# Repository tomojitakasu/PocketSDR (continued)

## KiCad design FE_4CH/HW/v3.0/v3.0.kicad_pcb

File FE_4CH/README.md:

# **Pocket SDR FE 4CH - An Open-Source GNSS SDR RF Frontend**

## **Overview**

Pocket SDR FE 4CH is an open-source GNSS SDR RF frontend device for Pocket SDR.
The device consists of 4 CH Maxim MAX2771 ([1]) GNSS RF front-end ICs (LNA, mixer,
filter, ADC, frequency synthesizer) and a Cypress EZ-USB FX3 USB 3.0 controller
([2], [3], [4]) to connect to host PCs. All the RF CHs are able to be configured for
GNSS L1 band (1525 - 1610 MHz), or GNSS L2/L5/L6 band (1160 - 1290 MHz).
The frequency of the reference oscillator (TCXO) is 24.000 MHz, and the ADC
sampling rate can be configured up to 48 Msps.

--------------------------------------------------------------------------------

## **Specifications**

* **Number of RF Inputs**: 1 CH
* **Number of RF Channels**: 4 CH
* **LO (PLL) Frequency**: 1525 ~ 1610 MHz (GNSS L1 band) or
                      1160 ~ 1290 MHz (GNSS L2/L5/L6 band)
* **IF Bandwidth**: 2.5 ~ 36 MHz
* **Sampling Rate**: 4, 6, 8, 10, 12, 16, 20, 24, 32, 40 or 48 Msps
* **Sampling Type**: I-sampling 2 or 3 bits, I/Q-sampling 2 bits
* **Host I/F**: USB 3.0 (USB 3.2 Gen1, super-speed 5Gbps), type-C
* **Power Supply**: 5V 240 mA, USB bus power

--------------------------------------------------------------------------------

## **Directory Structure and Contents**
```
FE_4CH --+-- FW     Pocket SDR FE 4CH F/W and build environment
         |   |
         |   +-- Packages
         |   +-- v3.0
         |       +-- .metadata
         |       +-- .project
         |       +-- pocket_fw_v3    ver.3.0
         |           +-- pocket_fw_v3.c  Source program of the F/W
         |           +-- gpif_conf.cyfx  GPIF II Designer file for the F/W
         |           +-- gpif_conf.h     header file generated by GPIF II Designer
         |           +-- pocket_usb_dscr.c USB device descriptors for the F/W
         |           +-- cyfx*.*         Cypress FX3 F/W framework
         |           +-- ...              
         |           +-- Release
         |               +-- pocket_fw_v3.img  Binary image of the F/W
         |               +-- ...
         |
         +-- HW     Pocket SDR FE 4CH hardware design data
             |
             +-- v3.0     ver.3.0 (PCB 4-layer, USB type-C)
                 +-- v3.0.kicad.*     KiCAD PCB and circuit design data
                 +-- v3.0.pretty      KiCAD module data
                 +-- v3.0_parts.xlsx  BOM (parts list) Excel data
                 +-- pocket_sdr_v3.0_sch.pdf circuit schematic PDF
                 +-- pocket_sdr_*.f3d Case panel Fusion 360 3D-CAD data
                 +-- pocket_sdr_v2.3-eagle-import.kicad_sym  KiCAD symbol data
                 +-- ...
```
--------------------------------------------------------------------------------

## **Rebuild F/W and Write F/W Image to Pocket SDR FE 4CH**

* Install Cypress EZ-USB FX3 Development Kit (ref [5]) to a Windows PC. As default,
it is installed to C:\Program Files (x86)\Cypress\EZ-USB FX3 SDK.
* Execute EZ USB Suite (EZ-USB FX3 SDK\1.3\Eclipse\ezUsbSuite.exe).
* Execute Menu File - Switch Workspace - Others, select <install_dir>\PocketSDR\FE_4CH\FW\v3.0
and open the workspace.
* Select pocket_fw_v3 in Project Explorer and execute Menu Project - Build All and
you can get a F/W image <install_dir>\PocketSDR\FE_4CH\FW/v3.0\pocket_fw_v3\Release\pocket_fw_v3.img.
* Disable EEPROM by connecting the J2 jumper pins on the Pocket SDR FE 4CH PCB and
attach the Pocket SDR FE 4CH via USB cable to the PC.
* Execute USB Control Center (EZ-USB FX3 SDK\1.3\bin\CyControl.exe).
* You can see "Cypress FX3 USB BootLoader Device".
* Re-enable EEPROM by disconnecting the J2 jumper pins on the Pocket SDR FE 4CH PCB.
* In USB Control Center, select "Cypress FX3 USB Bootloader Device", execute menu
Program - FX3 - I2C EEPROM, select the F/W image <install_dir>\PocketSDR\FE_4CH\FW\v3.0\pocket_fw_v3\Release\pocket_fw_v3.img
and open it.
* If you see "Programming succeeded." in status bar, the F/W is properly written
to the PocketSDR FE 4CH.

--------------------------------------------------------------------------------

## **References**

[1] Maxim integrated, MAX2771 Multiband Universal GNSS Receiver, July 2018

[2] Infineon, CYUSB301X, CYUSB201X, EZ-USB FX3 SuperSpeed USB Controller Datasheet,
Rev. Z, September 29, 2022

[3] Cypress Semiconductor, EZ-USB FX3 Technical Reference Manual, Rev.F, May 9, 2019

[4] Cypress Semiconductor, FX3 Programmers Manual, Rev.K

[5] Infineon, EZ-USB FX3 Software Development Kit
    (https://www.infineon.com/cms/jp/design-support/tools/sdk/usb-controllers-sdk/ez-usb-fx3-software-development-kit/)

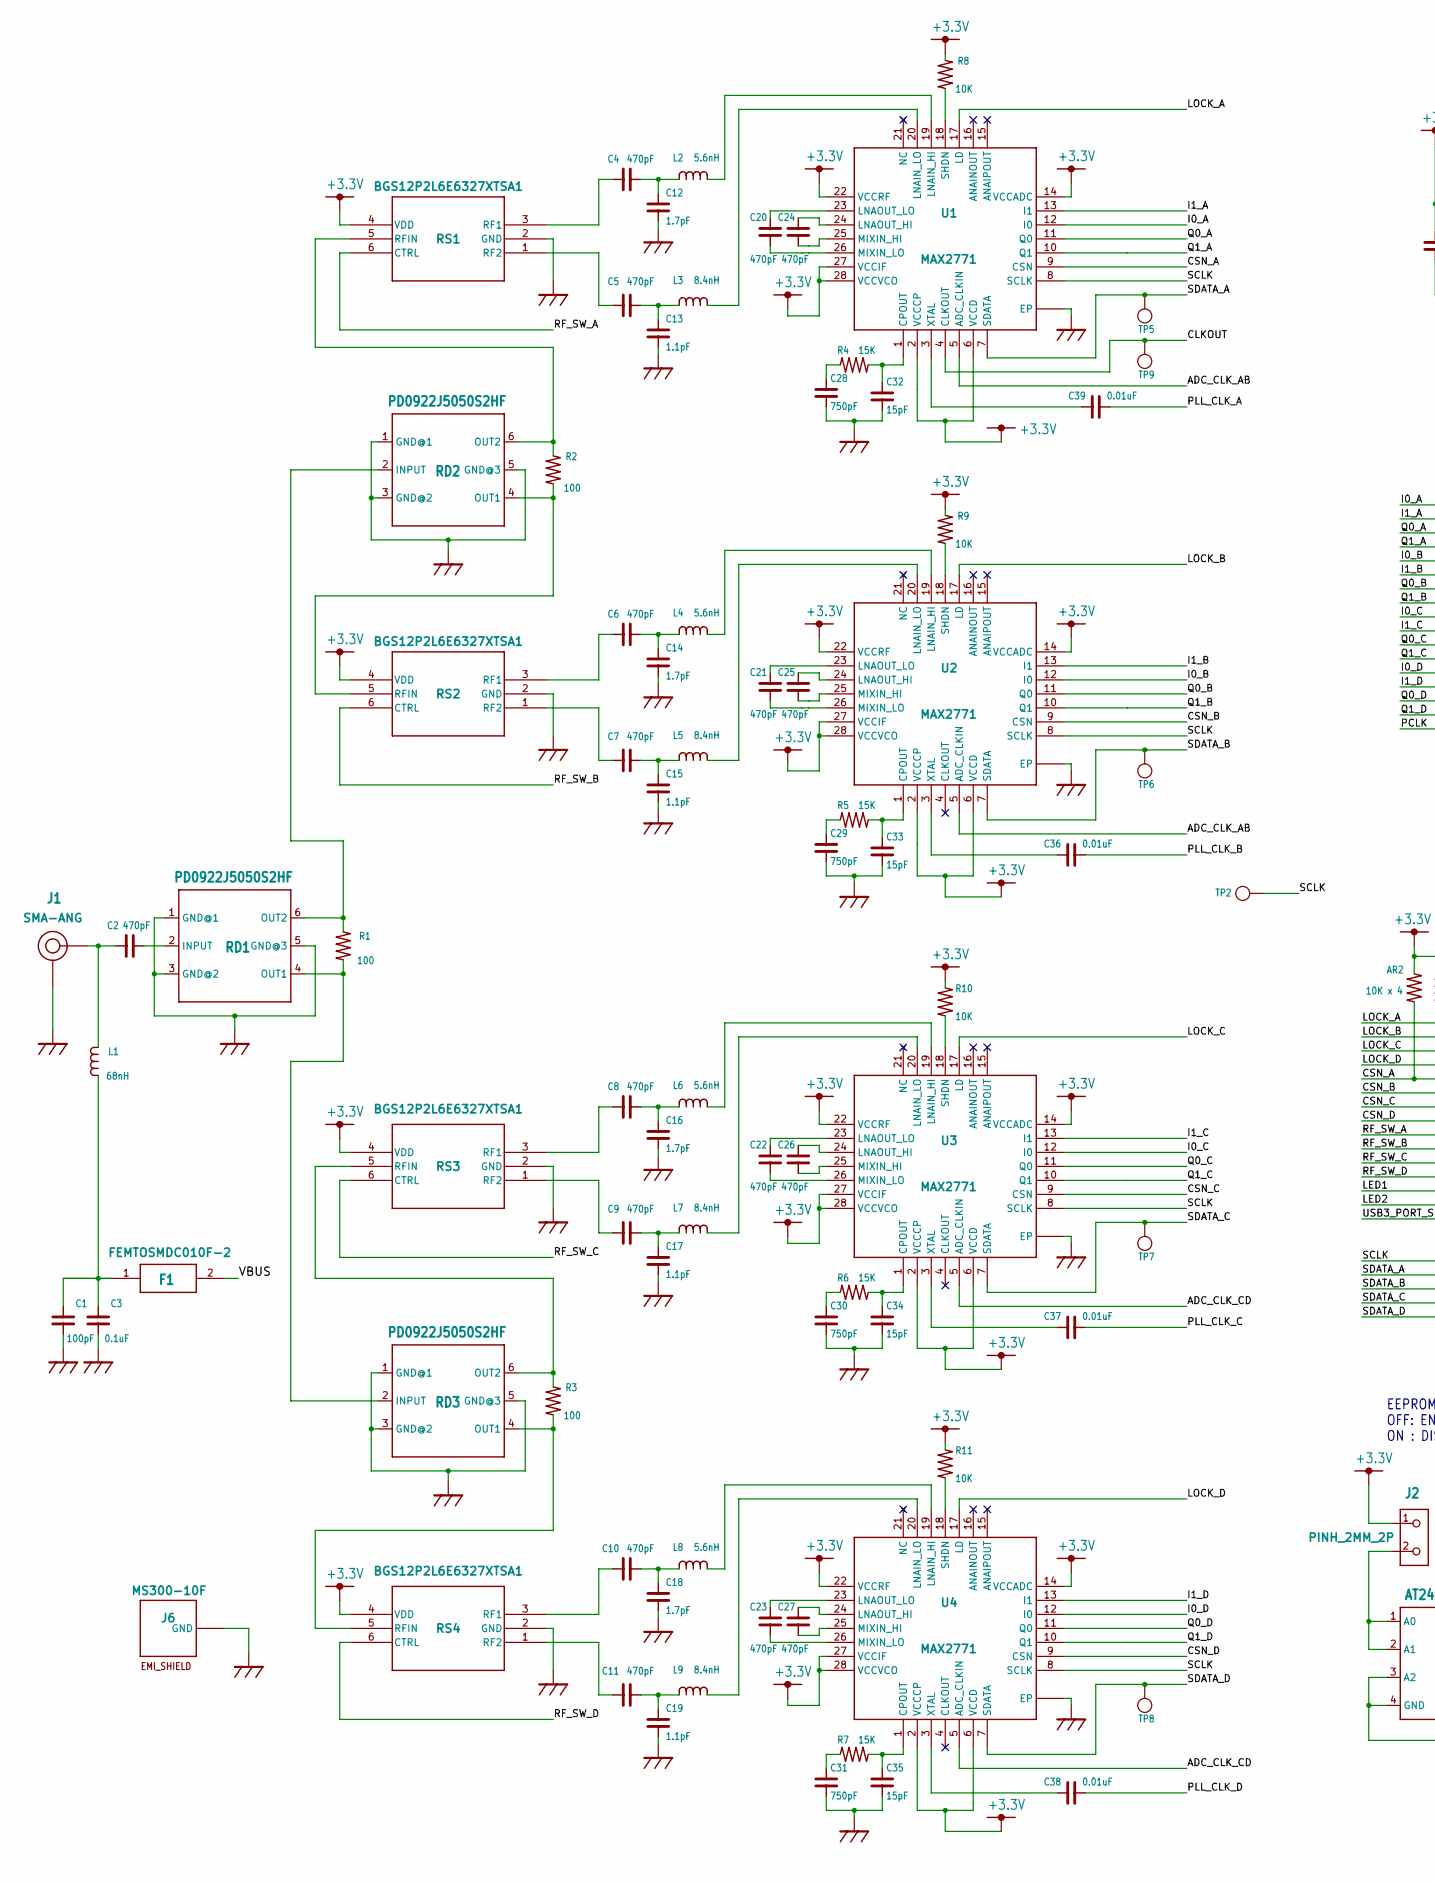
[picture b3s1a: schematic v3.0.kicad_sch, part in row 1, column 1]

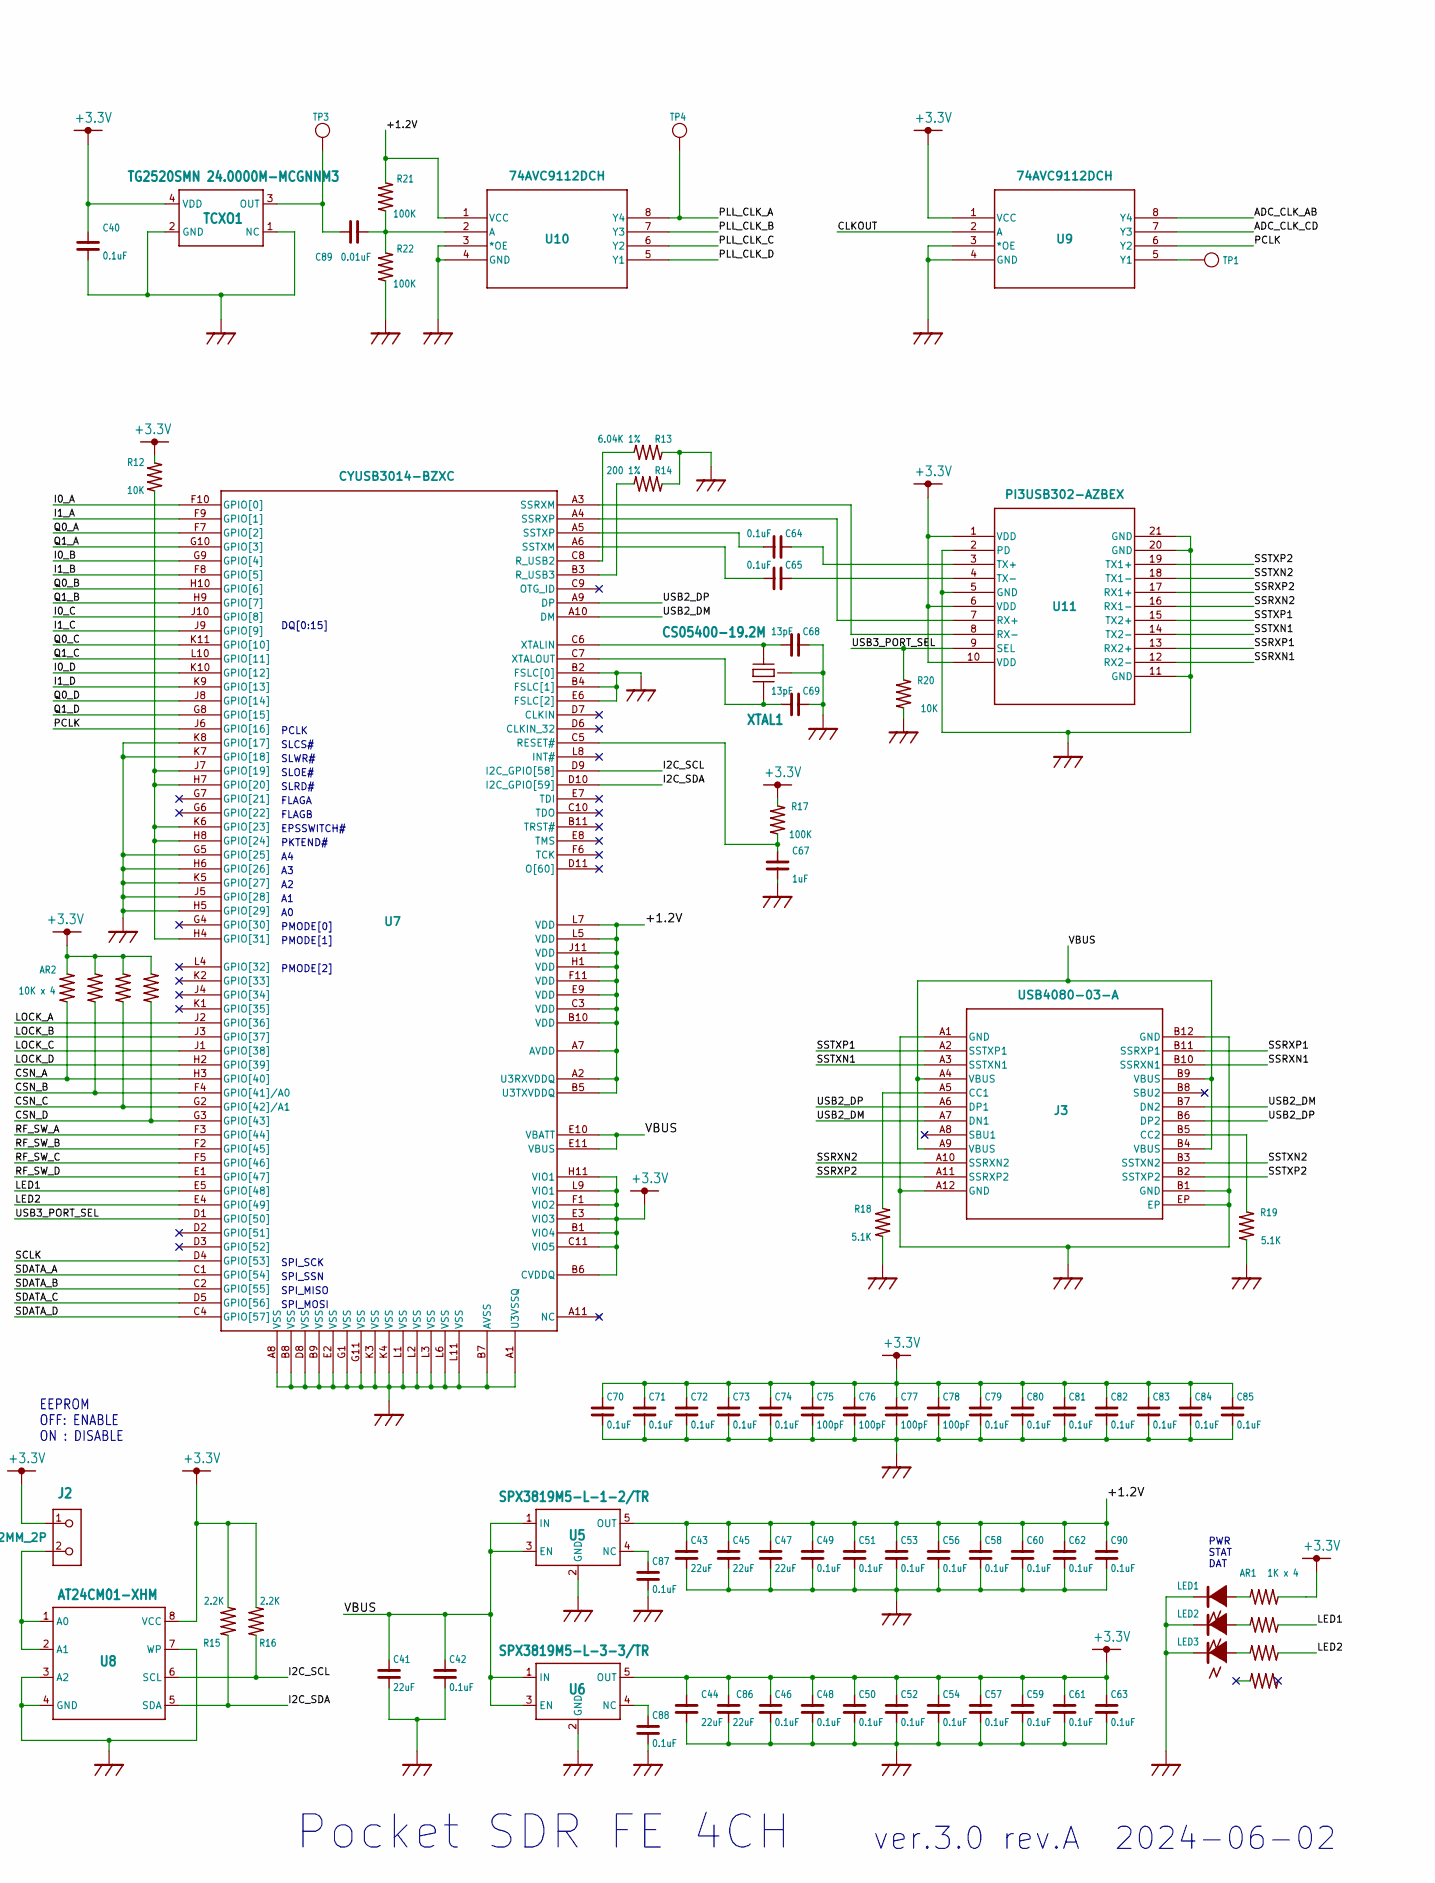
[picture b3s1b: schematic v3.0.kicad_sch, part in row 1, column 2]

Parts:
AR1: 1K x 4; EXB28V
AR2: 10K x 4; EXB28V
C1, C75, C76, C77, C78: 100pF; C1005
C2, C4, C5, C6, C7, C8, C9, C10, C11, C20, C21, C22, C23, C24, C25, C26, C27: 470pF; C1005
C3, C40, C42, C46, C48, C49, C50, C51, C52, C53, C54, C56, C57, C58, C59, C60, C61, C62, C63, C64, C65, C70, C71, C72, C73, C74, C79, C80, C81, C82, C83, C84, C85, C87, C88, C90: 0.1uF; C1005
C12, C14, C16, C18: 1.7pF; C1005
C13, C15, C17, C19: 1.1pF; C1005
C28, C29, C30, C31: 750pF; C1005
C32, C33, C34, C35: 15pF; C1005
C36, C37, C38, C39, C89: 0.01uF; C1005
C41, C43, C44, C45, C47, C86: 22uF; C1608
C67: 1uF; C1005
C68, C69: 13pF; C1005
F1: FEMTOSMDC010F-2; C1608
J1: SMA-ANG
J2: PINH_2MM_2P; PINH-2MM-2P
J3: USB4080-03-A; USB4080-03-A_GCT
J6: MS300-10F
L1: 68nH; C1608
L2, L4, L6, L8: 5.6nH; C1005
L3, L5, L7, L9: 8.4nH; C1005
LED1, LED2, LED3: LED1608; LED_1608
R1, R2, R3: 100; C1005
R4, R5, R6, R7: 15K; C1005
R8, R9, R10, R11, R12, R20: 10K; C1005
R13: 6.04K 1%; C1005
R14: 200 1%; C1005
R15, R16: 2.2K; C1005
R17, R21, R22: 100K; C1005
R18, R19: 5.1K; C1005
RD1, RD2, RD3: PD0922J5050S2HF; RF_DIV
RS1, RS2, RS3, RS4: BGS12P2L6E6327XTSA1; PG-TSLP-6-4_INF
TCXO1: TG2520SMN 24.0000M-MCGNNM3; TCXO
TP1, TP2, TP3, TP4, TP5, TP6, TP7, TP8, TP9: TP0.5
U1, U2, U3, U4: MAX2771; TQFN28
U5: SPX3819M5-L-1-2/TR; SOT23
U6: SPX3819M5-L-3-3/TR; SOT23
U7: CYUSB3014-BZXC; BGA-121
U8: AT24CM01-XHM; TSSOP_8P
U9, U10: 74AVC9112DCH; VSSOP8_SOT765-1_NEX
U11: PI3USB302-AZBEX; 20TQFN-ZB_PI3USB302-A_DIO
XTAL1: CS05400-19.2M; XTAL_SMD

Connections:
+3.3V: AR1.2, AR2.2, AR2.4, AR2.6, AR2.8, C40.1, C44.1, C46.1, C48.1, C50.1, C52.1, C54.1, C57.1, C59.1, C61.1, C63.1, C70.1, C71.1, C72.1, C73.1, C74.1, C75.1, C76.1, C77.1, C78.1, C79.1, C80.1, C81.1, C82.1, C83.1, C84.1, C85.1, C86.1, J2.1, R8.2, R9.2, R10.2, R11.2, R12.1, R15.2, R16.2, R17.2, RS1.4 (VDD), RS2.4 (VDD), RS3.4 (VDD), RS4.4 (VDD), TCXO1.4 (VDD), U1.2 (VCCCP), U1.6 (VCCD), U1.14 (VCCADC), U1.22 (VCCRF), U1.27 (VCCIF), U1.28 (VCCVCO), U2.2 (VCCCP), U2.6 (VCCD), U2.14 (VCCADC), U2.22 (VCCRF), U2.27 (VCCIF), U2.28 (VCCVCO), U3.2 (VCCCP), U3.6 (VCCD), U3.14 (VCCADC), U3.22 (VCCRF), U3.27 (VCCIF), U3.28 (VCCVCO), U4.2 (VCCCP), U4.6 (VCCD), U4.14 (VCCADC), U4.22 (VCCRF), U4.27 (VCCIF), U4.28 (VCCVCO), U6.5 (OUT), U7.B1 (VIO4), U7.B6 (CVDDQ), U7.C11 (VIO5), U7.E3 (VIO3), U7.F1 (VIO2), U7.H11 (VIO1), U7.L9 (VIO1), U8.8 (VCC), U9.1 (VCC), U11.1 (VDD), U11.6 (VDD), U11.10 (VDD)
/+1.2V: C43.1, C45.1, C47.1, C49.1, C51.1, C53.1, C56.1, C58.1, C60.1, C62.1, C90.1, R21.1, U5.5 (OUT), U7.A2 (U3RXVDDQ), U7.A7 (AVDD), U7.B5 (U3TXVDDQ), U7.B10 (VDD), U7.C3 (VDD), U7.E9 (VDD), U7.F11 (VDD), U7.H1 (VDD), U7.J11 (VDD), U7.L5 (VDD), U7.L7 (VDD), U10.1 (VCC)
/ADC_CLK_AB: U1.5 (ADC_CLKIN), U2.5 (ADC_CLKIN), U9.8 (Y4)
/ADC_CLK_CD: U3.5 (ADC_CLKIN), U4.5 (ADC_CLKIN), U9.7 (Y3)
/CLKOUT: TP9.1, U1.4 (CLKOUT), U9.2 (A)
/CSN_A: AR2.1, U1.9 (CSN), U7.H3 (GPIO[40])
/CSN_B: AR2.3, U2.9 (CSN), U7.F4 (GPIO[41]/A0)
/CSN_C: AR2.5, U3.9 (CSN), U7.G2 (GPIO[42]/A1)
/CSN_D: AR2.7, U4.9 (CSN), U7.G3 (GPIO[43])
/I0_A: U1.12 (I0), U7.F10 (GPIO[0])
/I0_B: U2.12 (I0), U7.G9 (GPIO[4])
/I0_C: U3.12 (I0), U7.J10 (GPIO[8])
/I0_D: U4.12 (I0), U7.K10 (GPIO[12])
/I1_A: U1.13 (I1), U7.F9 (GPIO[1])
/I1_B: U2.13 (I1), U7.F8 (GPIO[5])
/I1_C: U3.13 (I1), U7.J9 (GPIO[9])
/I1_D: U4.13 (I1), U7.K9 (GPIO[13])
/I2C_SCL: R16.1, U7.D9 (I2C_GPIO[58]), U8.6 (SCL)
/I2C_SDA: R15.1, U7.D10 (I2C_GPIO[59]), U8.5 (SDA)
/LED1: AR1.4, U7.E5 (GPIO[48])
/LED2: AR1.6, U7.E4 (GPIO[49])
/LOCK_A: U1.17 (LD), U7.J2 (GPIO[36])
/LOCK_B: U2.17 (LD), U7.J3 (GPIO[37])
/LOCK_C: U3.17 (LD), U7.J1 (GPIO[38])
/LOCK_D: U4.17 (LD), U7.H2 (GPIO[39])
/PCLK: U7.J6 (GPIO[16]), U9.6 (Y2)
/PLL_CLK_A: C39.1, TP4.1, U10.8 (Y4)
/PLL_CLK_B: C36.1, U10.7 (Y3)
/PLL_CLK_C: C37.1, U10.6 (Y2)
/PLL_CLK_D: C38.1, U10.5 (Y1)
/Q0_A: U1.11 (Q0), U7.F7 (GPIO[2])
/Q0_B: U2.11 (Q0), U7.H10 (GPIO[6])
/Q0_C: U3.11 (Q0), U7.K11 (GPIO[10])
/Q0_D: U4.11 (Q0), U7.J8 (GPIO[14])
/Q1_A: U1.10 (Q1), U7.G10 (GPIO[3])
/Q1_B: U2.10 (Q1), U7.H9 (GPIO[7])
/Q1_C: U3.10 (Q1), U7.L10 (GPIO[11])
/Q1_D: U4.10 (Q1), U7.G8 (GPIO[15])
/RF_SW_A: RS1.6 (CTRL), U7.F3 (GPIO[44])
/RF_SW_B: RS2.6 (CTRL), U7.F2 (GPIO[45])
/RF_SW_C: RS3.6 (CTRL), U7.F5 (GPIO[46])
/RF_SW_D: RS4.6 (CTRL), U7.E1 (GPIO[47])
/SCLK: TP2.1, U1.8 (SCLK), U2.8 (SCLK), U3.8 (SCLK), U4.8 (SCLK), U7.D4 (GPIO[53])
/SDATA_A: TP5.1, U1.7 (SDATA), U7.C1 (GPIO[54])
/SDATA_B: TP6.1, U2.7 (SDATA), U7.C2 (GPIO[55])
/SDATA_C: TP7.1, U3.7 (SDATA), U7.D5 (GPIO[56])
/SDATA_D: TP8.1, U4.7 (SDATA), U7.C4 (GPIO[57])
/SSRXN1: J3.B10 (SSRXN1), U11.12 (RX2-)
/SSRXN2: J3.A10 (SSRXN2), U11.16 (RX1-)
/SSRXP1: J3.B11 (SSRXP1), U11.13 (RX2+)
/SSRXP2: J3.A11 (SSRXP2), U11.17 (RX1+)
/SSTXN1: J3.A3 (SSTXN1), U11.14 (TX2-)
/SSTXN2: J3.B3 (SSTXN2), U11.18 (TX1-)
/SSTXP1: J3.A2 (SSTXP1), U11.15 (TX2+)
/SSTXP2: J3.B2 (SSTXP2), U11.19 (TX1+)
/USB2_DM: J3.A7 (DN1), J3.B7 (DN2), U7.A10 (DM)
/USB2_DP: J3.A6 (DP1), J3.B6 (DP2), U7.A9 (DP)
/USB3_PORT_SEL: R20.2, U7.D1 (GPIO[50]), U11.9 (SEL)
/VBUS: C41.1, C42.1, F1.2, J3.A4 (VBUS), J3.A9 (VBUS), J3.B4 (VBUS), J3.B9 (VBUS), U5.1 (IN), U5.3 (EN), U6.1 (IN), U6.3 (EN), U7.E10 (VBATT), U7.E11 (VBUS)
GND: C1.1, C3.1, C12.1, C13.1, C14.1, C15.1, C16.1, C17.1, C18.1, C19.1, C28.2, C29.2, C30.2, C31.2, C32.2, C33.2, C34.2, C35.2, C40.2, C41.2, C42.2, C43.2, C44.2, C45.2, C46.2, C47.2, C48.2, C49.2, C50.2, C51.2, C52.2, C53.2, C54.2, C56.2, C57.2, C58.2, C59.2, C60.2, C61.2, C62.2, C63.2, C67.2, C68.1, C69.1, C70.2, C71.2, C72.2, C73.2, C74.2, C75.2, C76.2, C77.2, C78.2, C79.2, C80.2, C81.2, C82.2, C83.2, C84.2, C85.2, C86.2, C87.2, C88.2, C90.2, J1.P2 (GND), J1.P3 (GND), J1.P4 (GND), J1.P5 (GND), J3.A1 (GND), J3.A12 (GND), J3.B1 (GND), J3.B12 (GND), J3.EP, J6.P1 (GND), LED1.2, LED2.2, LED3.2, R13.1, R14.1, R18.1, R19.1, R20.1, R22.2, RD1.1 (GND@1), RD1.3 (GND@2), RD1.5 (GND@3), RD2.1 (GND@1), RD2.3 (GND@2), RD2.5 (GND@3), RD3.1 (GND@1), RD3.3 (GND@2), RD3.5 (GND@3), RS1.2 (GND), RS2.2 (GND), RS3.2 (GND), RS4.2 (GND), TCXO1.1 (NC), TCXO1.2 (GND), U1.C1 (EP), U1.C2 (EP), U1.C3 (EP), U1.C4 (EP), U1.EP, U1.V1 (EP), U1.V2 (EP), U1.V3 (EP), U1.V4 (EP), U1.V5 (EP), U1.V6 (EP), U1.V7 (EP), U1.V8 (EP), U1.V9 (EP), U2.C1 (EP), U2.C2 (EP), U2.C3 (EP), U2.C4 (EP), U2.EP, U2.V1 (EP), U2.V2 (EP), U2.V3 (EP), U2.V4 (EP), U2.V5 (EP), U2.V6 (EP), U2.V7 (EP), U2.V8 (EP), U2.V9 (EP), U3.C1 (EP), U3.C2 (EP), U3.C3 (EP), U3.C4 (EP), U3.EP, U3.V1 (EP), U3.V2 (EP), U3.V3 (EP), U3.V4 (EP), U3.V5 (EP), U3.V6 (EP), U3.V7 (EP), U3.V8 (EP), U3.V9 (EP), U4.C1 (EP), U4.C2 (EP), U4.C3 (EP), U4.C4 (EP), U4.EP, U4.V1 (EP), U4.V2 (EP), U4.V3 (EP), U4.V4 (EP), U4.V5 (EP), U4.V6 (EP), U4.V7 (EP), U4.V8 (EP), U4.V9 (EP), U5.2 (GND), U6.2 (GND), U7.A1 (U3VSSQ), U7.A8 (VSS), U7.B2 (FSLC[0]), U7.B4 (FSLC[1]), U7.B7 (AVSS), U7.B8 (VSS), U7.B9 (VSS), U7.D8 (VSS), U7.E2 (VSS), U7.E6 (FSLC[2]), U7.G1 (VSS), U7.G5 (GPIO[25]), U7.G11 (VSS), U7.H5 (GPIO[29]), U7.H6 (GPIO[26]), U7.J5 (GPIO[28]), U7.K3 (VSS), U7.K4 (VSS), U7.K5 (GPIO[27]), U7.K7 (GPIO[18]), U7.K8 (GPIO[17]), U7.L1 (VSS), U7.L2 (VSS), U7.L3 (VSS), U7.L6 (VSS), U7.L11 (VSS), U8.3 (A2), U8.4 (GND), U8.7 (WP), U9.3 (*OE), U9.4 (GND), U10.3 (*OE), U10.4 (GND), U11.2 (PD), U11.5 (GND), U11.11 (GND), U11.20 (GND), U11.21 (GND), XTAL1.P2 (GND), XTAL1.P4 (GND)
unnamed: AR1.1, LED1.1 (+)
unnamed: AR1.3, LED2.1 (+)
unnamed: AR1.5, LED3.1 (+)
unnamed: C1.2, C3.2, F1.1, L1.1
unnamed: C2.1, J1.P1 (RF), L1.2
unnamed: J2.2, U8.1 (A0), U8.2 (A1)
unnamed: J3.A5 (CC1), R18.2
unnamed: J3.B5 (CC2), R19.2
unnamed: C4.2, C12.2, L2.1
unnamed: L2.2, U1.19 (LNAIN_HI)
unnamed: C5.2, C13.2, L3.1
unnamed: L3.2, U1.20 (LNAIN_LO)
unnamed: C6.2, C14.2, L4.1
unnamed: L4.2, U2.19 (LNAIN_HI)
unnamed: C7.2, C15.2, L5.1
unnamed: L5.2, U2.20 (LNAIN_LO)
unnamed: C8.2, C16.2, L6.1
unnamed: L6.2, U3.19 (LNAIN_HI)
unnamed: C9.2, C17.2, L7.1
unnamed: L7.2, U3.20 (LNAIN_LO)
unnamed: C10.2, C18.2, L8.1
unnamed: L8.2, U4.19 (LNAIN_HI)
unnamed: C11.2, C19.2, L9.1
unnamed: L9.2, U4.20 (LNAIN_LO)
unnamed: R1.1, RD1.4 (OUT1), RD3.2 (INPUT)
unnamed: R1.2, RD1.6 (OUT2), RD2.2 (INPUT)
unnamed: R2.1, RD2.4 (OUT1), RS2.5 (RFIN)
unnamed: R2.2, RD2.6 (OUT2), RS1.5 (RFIN)
unnamed: R3.1, RD3.4 (OUT1), RS4.5 (RFIN)
unnamed: R3.2, RD3.6 (OUT2), RS3.5 (RFIN)
unnamed: C28.1, R4.1
unnamed: C32.1, R4.2, U1.1 (CPOUT)
unnamed: C29.1, R5.1
unnamed: C33.1, R5.2, U2.1 (CPOUT)
unnamed: C30.1, R6.1
unnamed: C34.1, R6.2, U3.1 (CPOUT)
unnamed: C31.1, R7.1
unnamed: C35.1, R7.2, U4.1 (CPOUT)
unnamed: R8.1, U1.18 (SHDN)
unnamed: R9.1, U2.18 (SHDN)
unnamed: R10.1, U3.18 (SHDN)
unnamed: R11.1, U4.18 (SHDN)
unnamed: R12.2, U7.H4 (GPIO[31]), U7.H7 (GPIO[20]), U7.H8 (GPIO[24]), U7.J7 (GPIO[19]), U7.K6 (GPIO[23])
unnamed: R13.2, U7.C8 (R_USB2)
unnamed: R14.2, U7.B3 (R_USB3)
unnamed: C67.1, R17.1, U7.C5 (RESET#)
unnamed: C89.2, R21.2, R22.1, U10.2 (A)
unnamed: C2.2, RD1.2 (INPUT)
unnamed: C4.1, RS1.3 (RF1)
unnamed: C5.1, RS1.1 (RF2)
unnamed: C6.1, RS2.3 (RF1)
unnamed: C7.1, RS2.1 (RF2)
unnamed: C8.1, RS3.3 (RF1)
unnamed: C9.1, RS3.1 (RF2)
unnamed: C10.1, RS4.3 (RF1)
unnamed: C11.1, RS4.1 (RF2)
unnamed: C89.1, TCXO1.3 (OUT), TP3.1
unnamed: C24.1, U1.24 (LNAOUT_HI)
unnamed: C20.1, U1.23 (LNAOUT_LO)
unnamed: C24.2, U1.25 (MIXIN_HI)
unnamed: C20.2, U1.26 (MIXIN_LO)
unnamed: C39.2, U1.3 (XTAL)
unnamed: C25.1, U2.24 (LNAOUT_HI)
unnamed: C21.1, U2.23 (LNAOUT_LO)
unnamed: C25.2, U2.25 (MIXIN_HI)
unnamed: C21.2, U2.26 (MIXIN_LO)
unnamed: C36.2, U2.3 (XTAL)
unnamed: C26.1, U3.24 (LNAOUT_HI)
unnamed: C22.1, U3.23 (LNAOUT_LO)
unnamed: C26.2, U3.25 (MIXIN_HI)
unnamed: C22.2, U3.26 (MIXIN_LO)
unnamed: C37.2, U3.3 (XTAL)
unnamed: C27.1, U4.24 (LNAOUT_HI)
unnamed: C23.1, U4.23 (LNAOUT_LO)
unnamed: C27.2, U4.25 (MIXIN_HI)
unnamed: C23.2, U4.26 (MIXIN_LO)
unnamed: C38.2, U4.3 (XTAL)
unnamed: C87.1, U5.4 (NC)
unnamed: C88.1, U6.4 (NC)
unnamed: C65.2, U7.A6 (SSTXM)
unnamed: C64.2, U7.A5 (SSTXP)
unnamed: C68.2, U7.C6 (XTALIN), XTAL1.P1 (XTAL1)
unnamed: C69.2, U7.C7 (XTALOUT), XTAL1.P3 (XTAL2)
unnamed: TP1.1, U9.5 (Y1)
unnamed: U7.A4 (SSRXP), U11.7 (RX+)
unnamed: U7.A3 (SSRXM), U11.8 (RX-)
unnamed: C64.1, U11.3 (TX+)
unnamed: C65.1, U11.4 (TX-)

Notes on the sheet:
PCLK
EPSSWITCH#
SPI_SSN
PMODE[1]
DQ[0:15]
Pocket SDR FE 4CH
PMODE[0]
EEPROM OFF: ENABLE ON : DISABLE
SPI_SCK
SPI_MOSI
SLRD#
SLOE#
SLCS#
PMODE[2]
PWR STAT DAT
SLWR#
PKTEND#
ver.3.0 rev.A 2024-06-02
SPI_MISO
FLAGA
FLAGB

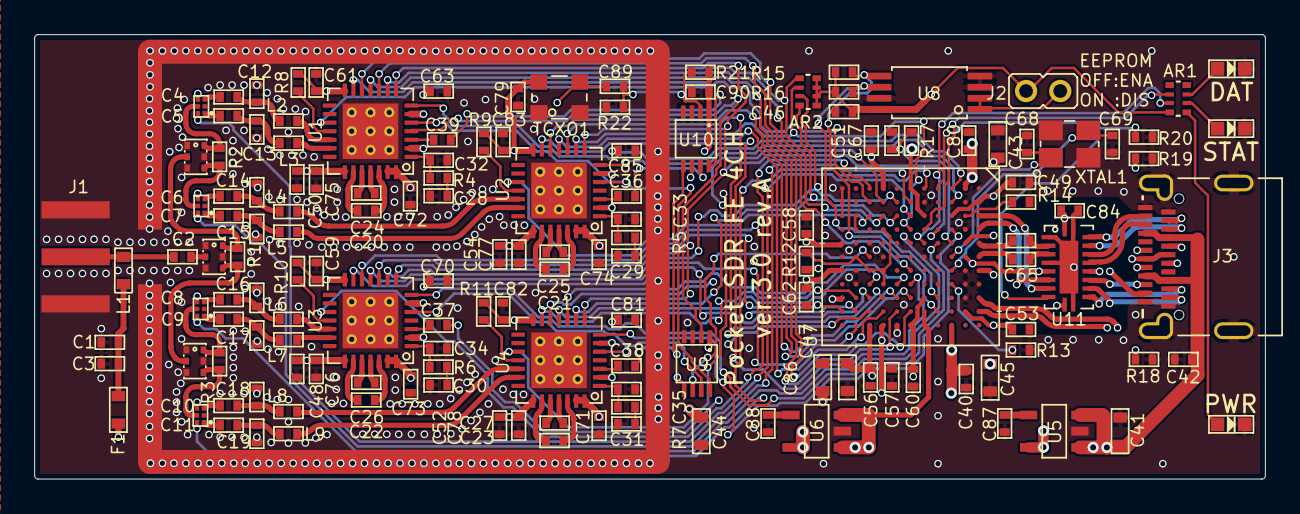
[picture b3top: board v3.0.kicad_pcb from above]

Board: 4 copper layers, 72.0 x 26.0 mm, 158 parts (0 on the bottom side), 148 nets.

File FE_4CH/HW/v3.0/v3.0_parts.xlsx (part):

No | Ref | Value | Package | Qnty | Assy | Supplier | Supplier Part # | Digikey Part # | Price | Total | URL
1 | U1, U2, U3, U4 | RF RX GNSS 1.227/1.575GHZ | TQFN28 | 4 | 4 | Maxim | MAX2771ETI+ | MAX2771ETI+-ND | 1631 | 6524 | https://www.digikey.jp/products/ja?keywords=MAX2771ETI%2B-ND
2 | U5 | LDO 1.2V 500mA | SOT23-5 | 1 | 1 | MaxLinear | SPX3819M5-L-1-2/TR | 1016-1872-1-ND | 92 | 92 | https://www.digikey.jp/ja/products/detail/maxlinear-inc/SPX3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
3 | U6 | LDO 3.3V 500mA | SOT23-5 | 1 | 1 | MaxLinear | SPX3819M5-L-3-3/TR | 1016-1873-1-ND | 92 | 92 | https://www.digikey.jp/ja/products/detail/maxlinear-inc/SPX3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
4 | U7 | EZ-USB FX3 USB 3.0 RAM 512KB | 121-TFBGA | 1 | 1 | Cypress | CYUSB3014-BZXC | 448-CYUSB3014-BZXC-ND | 4770 | 4770 | https://www.digikey.jp/ja/products/detail/infineon-technolog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
5 | U8 | I2C EEPROM 1MBIT | 8-TSSOP | 1 | 1 | Microchip | AT24CM01-XHM-T | AT24CM01-XHM-TCT-ND | 291 | 291 | https://www.digikey.jp/ja/products/detail/microchip-technolo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
6 | U9, U10 | IC CLK BUFFER 1:4 | 8-VSSOP | 2 | 2 | Nexperia | 74AVC9112DCH | 1727-7845-1-ND | 99 | 198 | https://www.digikey.jp/ja/products/detail/nexperia-usa-inc/7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
7 | U11 | IC MUX/DEMUX USB 3.0 | 20TQFN | 1 | 1 | Diodes | PI3USB302-AZBEX | PI3USB302-AZBEXCT-ND | 288 | 288 | https://www.digikey.jp/ja/products/detail/diodes-incorporate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
8 | RD1, RD2, RD3 | RF PWR DVDR 950MHZ-2.15GHZ | 2.04 x 1.29 SMD | 3 | 3 | TTM | PD0922J5050S2HF | 1173-1094-1-ND | 160 | 480 | https://www.digikey.jp/product-detail/ja/anaren/PD0922J5050S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
9 | RS1, RS2, RS3, RS4 | IC RF SWITCH SPDT 6GHZ | 6-XFDFN | 4 | 4 | Infineon | BGS12P2L6E6327XTSA1 | 448-BGS12P2L6E6327XTSA1CT-ND | 66 | 264 | https://www.digikey.jp/ja/products/detail/infineon-technolog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
10 | TCXO1 | TCXO 24.000 MHz 0.5ppm Clipped-sine | 2.5 x 2 SMD | 1 | 1 | Epson | TG2520SMN 24.0000M-MCGNNM3 | - | 526.29999999999995 | 526.29999999999995 | https://www.mouser.jp/ProductDetail/Epson-Timing/TG2520SMN-2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
11 | XTAL1 | XTAL 19.2MHz | 2.5 x 2 SMD | 1 | 1 | NDK | CS05400-19.2M | 644-CS05400-19.2MCT-ND | 134 | 134 | https://www.digikey.jp/ja/products/detail/ndk-america-inc/CS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
12 | C1, C75, C76, C77, C78 | 100pF | C1005 | 5 | 5 | Kyocera | KGM05ACG1H101JH | 478-KGM05ACG1H101JHCT-ND | 3.7 | 18.5 | https://www.digikey.jp/ja/products/detail/kyocera-avx/KGM05A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
13 | C2, C4, C5, C6, C7, C8, C9, C10, C11, C20, C21, C22, C23, C24, C25, C26, C27 | 470pF | C1005 | 17 | 17 | Kyocera | KGM05AR71H471KH | 478-KGM05AR71H471KHCT-ND | 4.5 | 76.5 | https://www.digikey.jp/ja/products/detail/kyocera-avx/KGM05A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
14 | C3, C40, C42, C46, C48, C49, C50, C51, C52, C53, C54, C56, C57, C58, C59, C60, 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 | 0.1uF | C1005 | 36 | 36 | Kyocera | KGM05AR71C104KH | 478-KGM05AR71C104KHCT-ND | 2.2000000000000002 | 79.2 | https://www.digikey.jp/ja/products/detail/kyocera-avx/KGM05A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
15 | C12, C14, C16, C18 | 1.7pF | C1005 | 4 | 4 | Murata | GJM1555C1H1R7BB01D | 490-6074-1-ND | 10.6 | 42.4 | https://www.digikey.jp/ja/products/detail/murata-electronics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
16 | C13, C15, C17, C19 | 1.1pF | C1005 | 4 | 4 | YAGEO | CC0402BRNPO9BN1R1 | 311-3321-1-ND | 6.2 | 24.8 | https://www.digikey.jp/ja/products/detail/yageo/CC0402BRNPO9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
17 | C28, C29, C30, C31 | 750pF | C1005 | 4 | 4 | Taiyo Yuden | UMK105CH751JVHF | 587-5098-1-ND | 11.1 | 44.4 | https://www.digikey.jp/ja/products/detail/taiyo-yuden/UMK105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
18 | C32, C33, C34, C35 | 15pF | C1005 | 4 | 4 | Kyocera | KGM05ACG1H150JH | 478-KGM05ACG1H150JHCT-ND | 5.0999999999999996 | 20.399999999999999 | https://www.digikey.jp/ja/products/detail/kyocera-avx/KGM05A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
19 | C36, C37, C38, C39, C89 | 0.01uF | C1005 | 5 | 4 | Kyocera | KGM05AR71C103KH | 478-KGM05AR71C103KHCT-ND | 2 | 10 | https://www.digikey.jp/ja/products/detail/kyocera-avx/KGM05A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
20 | C41, C43, C44, C45, C47, C86 | 22uF | C1608 | 6 | 6 | Murata | GRM188R61A226ME15D | 490-10476-1-ND | 22.7 | 136.19999999999999 | https://www.digikey.jp/ja/products/detail/murata-electronics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
21 | C67 | 1uF | C1005 | 1 | 1 | Kyocera | KGM05AR51A105KH | 478-KGM05AR51A105KHCT-ND | 11 | 11 | https://www.digikey.jp/ja/products/detail/kyocera-avx/KGM05A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
22 | C68, C69 | 13pF | C1005 | 2 | 2 | Murata | GJM1555C1H130FB01D | 490-GJM1555C1H130FB01DCT-ND | 18.2 | 36.4 | https://www.digikey.jp/ja/products/detail/murata-electronics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
23 | L1 | 68nH | L1608 | 1 | 1 | Murata | LQW18AN68NJ00D | 490-1178-1-ND | 24 | 24 | https://www.digikey.jp/ja/products/detail/murata-electronics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
24 | L2, L4, L6, L8 | 5.6nF | L1005 | 4 | 4 | Murata | LQW15AN5N6C8ZD | 490-15522-1-ND | 34 | 136 | https://www.digikey.jp/ja/products/detail/murata-electronics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
25 | L3, L5, L7, L9 | 8.4nF | L1005 | 4 | 4 | Murata | LQW15AN8N4G8ZD | 490-15595-1-ND | 37 | 148 | https://www.digikey.jp/ja/products/detail/murata-electronics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
26 | R1, R2, R3 | 100 | R1005 | 3 | 3 | YAGEO | RC0402JR-07100RL | 311-100JRCT-ND | 2.9 | 8.6999999999999993 | https://www.digikey.jp/ja/products/detail/yageo/RC0402JR-071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
27 | R4, R5, R6, R7 | 15K | R1005 | 4 | 4 | YAGEO | RC0402JR-0715KL | 311-15KJRCT-ND | 2.8 | 11.2 | https://www.digikey.jp/ja/products/detail/yageo/RC0402JR-071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
28 | R8, R9, R10, R11, R12, R20 | 10K | R1005 | 6 | 6 | YAGEO | RC0402JR-0710KL | 311-10KJRCT-ND | 2.8 | 16.799999999999997 | https://www.digikey.jp/ja/products/detail/yageo/RC0402JR-071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
29 | R13 | 6.04K 1% | R1005 | 1 | 1 | YAGEO | RC0402FR-076K04L | YAG2293CT-ND | 2.4 | 2.4 | https://www.digikey.jp/ja/products/detail/yageo/RC0402FR-076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
30 | R14 | 200 1% | R1005 | 1 | 1 | YAGEO | RC0402FR-07200RL | 311-200LRCT-ND | 2.4 | 2.4 | https://www.digikey.jp/ja/products/detail/yageo/RC0402FR-072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
31 | R15, R16 | 2.2K | R1005 | 2 | 2 | YAGEO | RC0402JR-072K2L | 311-2.2KJRCT-ND | 2.8 | 5.6 | https://www.digikey.jp/ja/products/detail/yageo/RC0402JR-072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
32 | R17, R21, R22 | 100K | R1005 | 3 | 1 | YAGEO | RC0402JR-07100KL | 311-100KJRCT-ND | 2.8 | 8.3999999999999986 | https://www.digikey.jp/ja/products/detail/yageo/RC0402JR-071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
33 | R18, R19 | 5.1K | R1005 | 2 | 2 | YAGEO | RC0402FR-135K1L | 13-RC0402FR-135K1LCT-ND | 2.2999999999999998 | 4.5999999999999996 | https://www.digikey.jp/ja/products/detail/yageo/RC0402FR-135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
34 | AR1 | 1K x 4 | ARRAY_REG__EXB28V | 1 | 1 | Panasonic | EXB-28V102JX | Y7102CT-ND | 16 | 16 | https://www.digikey.jp/products/ja?keywords=Y7102CT-ND
35 | AR2 | 10K x 4 | ARRAY_REG__EXB28V | 1 | 1 | Panasonic | EXB-28V103JX | Y7103CT-ND | 17 | 17 | https://www.digikey.jp/ja/products/detail/panasonic-electron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
36 | LED1, LED2, LED3 | LED white | LED1608 | 3 | 3 | QT Brightek | QBLP601-IW | 1516-1057-1-ND | 59 | 177 | https://www.digikey.jp/ja/products/detail/qt-brightek-qtb/QB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
37 | F1 | PolySwitch 12V, 8 Ohm, Trip 250 mA | POLYSW1608 | 1 | 1 | Littelfuse Inc | FEMTOSMDC010F-2 | FEMTOSMDC010F-2 | 123 | 123 | https://www.digikey.jp/ja/products/detail/littelfuse-inc/FEM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
38 | J1 | SMA JACK EDGE MNT | SMA-ANG | 1 | 0 | uxcell | - | - | 157.6 | 157.6 | Amazon
39 | J2 | PINH_2MM_2P | PINH_2MM_2P | 1 | 0 | Harwin | M22-2510205 | 952-1311-ND | 31 | 31 | https://www.digikey.jp/ja/products/detail/harwin-inc/M22-251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
40 | J2-S | CONN SHUNT 2MM | CONN SHUNT 2MM | 1 | 0 | Sullins Connector | SPN02SYBN-RC | S3404-ND | 20 | 20 | https://www.digikey.jp/ja/products/detail/sullins-connector-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
41 | J3 | USB Type-C Receptacle USB 3.2 24p | USB Type-C Receptacle | 1 | 1 | GCT | USB4080-03-A | 2073-USB4080-03-ACT-ND | 188 | 188 | https://www.digikey.jp/ja/products/detail/gct/USB4080-03-A/14659819
42 | J6 | RF SHIELD 0.961"X1.181" SOLDER | MS300-10F | 1 | 0 | Masach | MS300-10F | 2333-MS300-10F-ND | 246 | 246 | https://www.digikey.jp/ja/products/detail/masach-tech-ltd/MS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
43 | J6-S | RF SHIELD 0.984X1.205" SNAP FIT | MS300-10C | 1 | 0 | Masach | MS300-10C | 2333-MS300-10C-ND | 246 | 246 | https://www.digikey.jp/ja/products/detail/masach-tech-ltd/MS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
 | Subtotal |  |  |  | 143 |  |  |  |  | 15748.8
 | PCB | FR4, 4-layer | 72 x 26 x 1.6 mm | 1 | 0 | JLCPCB |  |  | 447.02700000000004 | 447.02700000000004 | https://jlcpcb.com/ | 10pcs (PCB+STENCIL+SHIPPING)
 | PCB Assy |  |  | 1 | 0 |  |  |  | 1432.2357 | 1432.2357
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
